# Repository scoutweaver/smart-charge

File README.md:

# smart-charge
This is the MCU coding which interacts with Raspberry pi sensors and a PostgreSQL database.
This system wil optimize the life of lithium ion batteries by enhancing the charging system.

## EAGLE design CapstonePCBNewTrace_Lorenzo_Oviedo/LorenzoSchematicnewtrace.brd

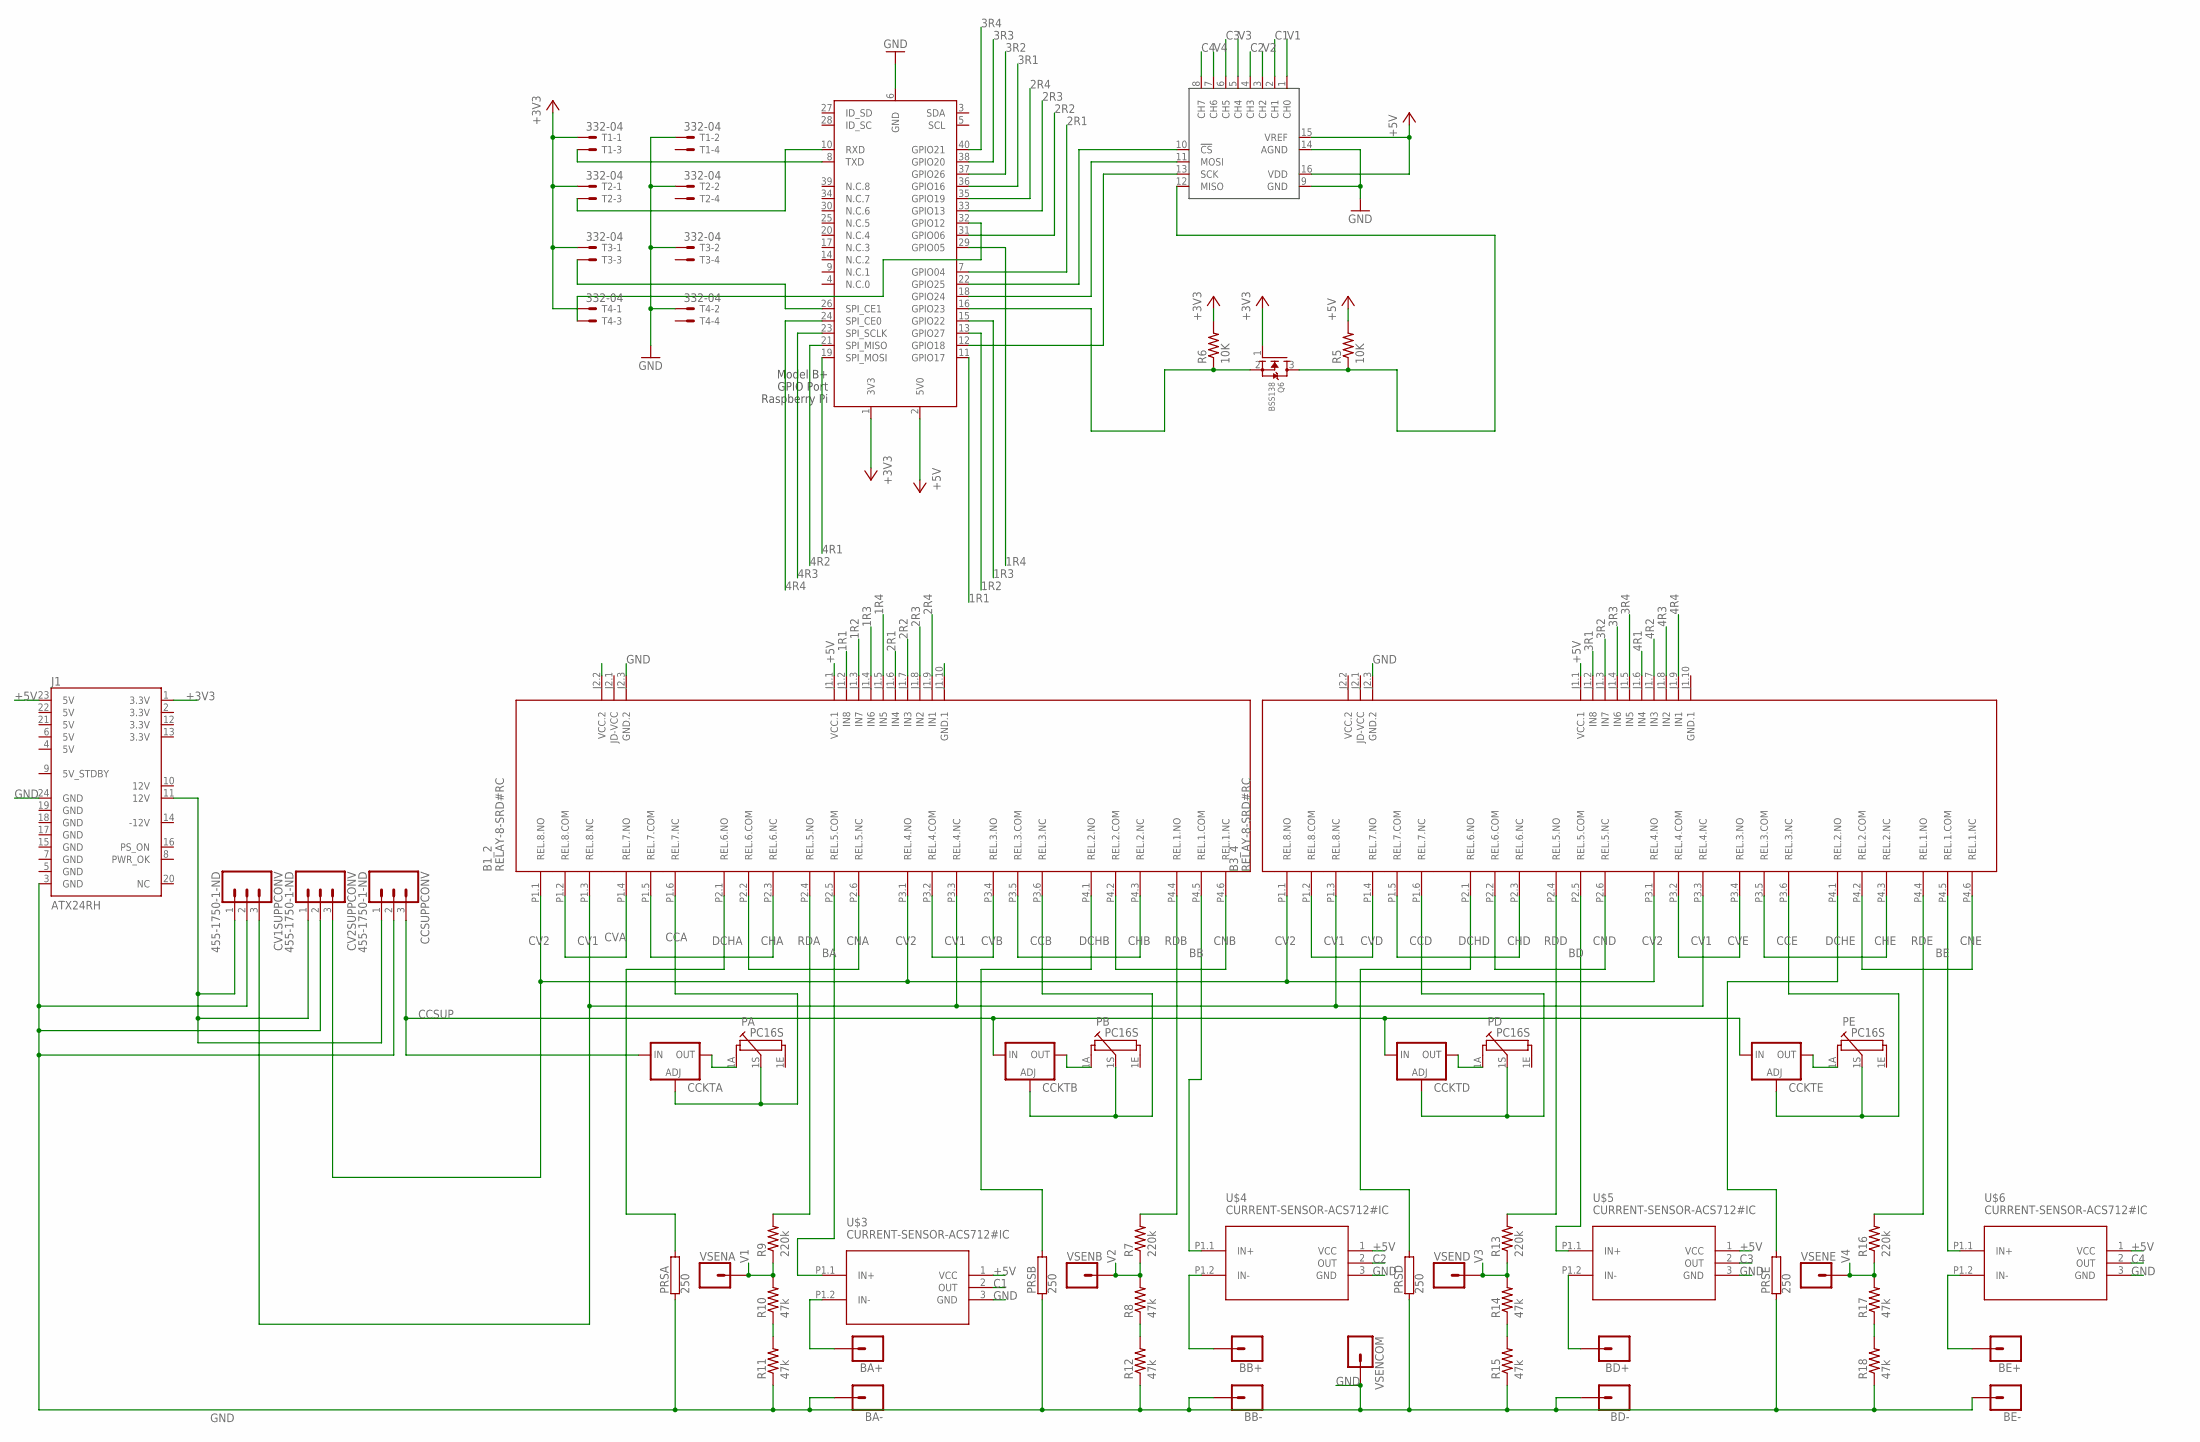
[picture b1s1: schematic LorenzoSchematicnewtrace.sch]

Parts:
ADC: MCP3008P; DIL16
B1_2, B3_4: RELAY-8-SRD#RC
BA+: CONN_01; 1X01
BA-: CONN_01; 1X01
BB+: CONN_01; 1X01
BB-: CONN_01; 1X01
BD+: CONN_01; 1X01
BD-: CONN_01; 1X01
BE+: CONN_01; 1X01
BE-: CONN_01; 1X01
CCKTA: LM317TL; 317TL
CCKTB: LM317TL; 317TL
CCKTD: LM317TL; 317TL
CCKTE: LM317TL; 317TL
CCSUPPCONV: 455-1750-1-ND; 1X03
CV1SUPPCONV, CV2SUPPCONV: 455-1750-1-ND; 1X03
J1: ATX24RH; ATX24_RIGHT_ANGLE
PA: PC16S
PB: PC16S
PD: PC16S
PE: PC16S
PRSA: 250; KH208-8
PRSB: 250; KH208-8
PRSD: 250; KH208-8
PRSE: 250; KH208-8
Q6: BSS138; SOT23
R5, R6: 10K; R0805
R7, R9, R13, R16: 220k; 0207/12
R8, R10, R11, R12, R14, R15, R17, R18: 47k; 0207/12
T1, T2, T3, T4: 332-04
U$3, U$4, U$5, U$6: CURRENT-SENSOR-ACS712#IC
VSENA: CONN_01; 1X01
VSENB: CONN_01; 1X01
VSENCOM: CONN_01; 1X01
VSEND: CONN_01; 1X01
VSENE: CONN_01; 1X01
X2: RASPI_BOARD_B+_E4; RASPI_BOARD_B+_EDGES_4DRILL

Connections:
1R1: B1_2.J1.2 (IN8), X2.11 (GPIO17)
1R2: B1_2.J1.3 (IN7), X2.13 (GPIO27)
1R3: B1_2.J1.4 (IN6), X2.15 (GPIO22)
1R4: B1_2.J1.5 (IN5), X2.29 (GPIO05)
2R1: B1_2.J1.6 (IN4), X2.7 (GPIO04)
2R2: B1_2.J1.7 (IN3), X2.31 (GPIO06)
2R3: B1_2.J1.8 (IN2), X2.33 (GPIO13)
2R4: B1_2.J1.9 (IN1), X2.35 (GPIO19)
3R1: B3_4.J1.2 (IN8), X2.36 (GPIO16)
3R2: B3_4.J1.3 (IN7), X2.37 (GPIO26)
3R3: B3_4.J1.4 (IN6), X2.38 (GPIO20)
3R4: B3_4.J1.5 (IN5), X2.40 (GPIO21)
4R1: B3_4.J1.6 (IN4), X2.19 (SPI_MOSI)
4R2: B3_4.J1.7 (IN3), X2.21 (SPI_MISO)
4R3: B3_4.J1.8 (IN2), X2.23 (SPI_SCLK)
4R4: B3_4.J1.9 (IN1), X2.24 (SPI_CE0)
12V: CCSUPPCONV.1, CV1SUPPCONV.1, CV2SUPPCONV.1, J1.11 (12V)
+3V3: J1.1 (3.3V), Q6.1 (G), R6.2, T1.1, T2.1, T3.1, T4.1, X2.1 (3V3)
+5V: ADC.15 (VREF), ADC.16 (VDD), B1_2.J1.1 (VCC.1), B3_4.J1.1 (VCC.1), J1.23 (5V), R5.2, U$3.1 (VCC), U$4.1 (VCC), U$5.1 (VCC), U$6.1 (VCC), X2.2 (5V0)
BA: B1_2.P2.5 (REL.5.COM), U$3.P1.1 (IN+)
BB: B1_2.P4.5 (REL.1.COM), U$4.P1.1 (IN+)
BD: B3_4.P2.5 (REL.5.COM), U$5.P1.1 (IN+)
BE: B3_4.P4.5 (REL.1.COM), U$6.P1.1 (IN+)
C1: ADC.2 (CH1), U$3.2 (OUT)
C2: ADC.4 (CH3), U$4.2 (OUT)
C3: ADC.6 (CH5), U$5.2 (OUT)
C4: ADC.8 (CH7), U$6.2 (OUT)
CCA: B1_2.P1.6 (REL.7.NC), CCKTA.1 (ADJ), PA.1S
CCB: B1_2.P3.6 (REL.3.NC), CCKTB.1 (ADJ), PB.1S
CCD: B3_4.P1.6 (REL.7.NC), CCKTD.1 (ADJ), PD.1S
CCE: B3_4.P3.6 (REL.3.NC), CCKTE.1 (ADJ), PE.1S
CCSUP: CCKTA.3 (IN), CCKTB.3 (IN), CCKTD.3 (IN), CCKTE.3 (IN), CCSUPPCONV.3
CHA: B1_2.P1.5 (REL.7.COM), B1_2.P2.3 (REL.6.NC)
CHB: B1_2.P3.5 (REL.3.COM), B1_2.P4.3 (REL.2.NC)
CHD: B3_4.P1.5 (REL.7.COM), B3_4.P2.3 (REL.6.NC)
CHE: B3_4.P3.5 (REL.3.COM), B3_4.P4.3 (REL.2.NC)
CNA: B1_2.P2.2 (REL.6.COM), B1_2.P2.6 (REL.5.NC)
CNB: B1_2.P4.2 (REL.2.COM), B1_2.P4.6 (REL.1.NC)
CND: B3_4.P2.2 (REL.6.COM), B3_4.P2.6 (REL.5.NC)
CNE: B3_4.P4.2 (REL.2.COM), B3_4.P4.6 (REL.1.NC)
CV1: B1_2.P1.3 (REL.8.NC), B1_2.P3.3 (REL.4.NC), B3_4.P1.3 (REL.8.NC), B3_4.P3.3 (REL.4.NC), CV1SUPPCONV.3
CV2: B1_2.P1.1 (REL.8.NO), B1_2.P3.1 (REL.4.NO), B3_4.P1.1 (REL.8.NO), B3_4.P3.1 (REL.4.NO), CV2SUPPCONV.3
CVA: B1_2.P1.2 (REL.8.COM), B1_2.P1.4 (REL.7.NO)
CVB: B1_2.P3.2 (REL.4.COM), B1_2.P3.4 (REL.3.NO)
CVD: B3_4.P1.2 (REL.8.COM), B3_4.P1.4 (REL.7.NO)
CVE: B3_4.P3.2 (REL.4.COM), B3_4.P3.4 (REL.3.NO)
DCHA: B1_2.P2.1 (REL.6.NO), PRSA.2
DCHB: B1_2.P4.1 (REL.2.NO), PRSB.2
DCHD: B3_4.P2.1 (REL.6.NO), PRSD.2
DCHE: B3_4.P4.1 (REL.2.NO), PRSE.2
GND: ADC.9 (GND), ADC.14 (AGND), B1_2.J2.3 (GND.2), B3_4.J2.3 (GND.2), BA-.1, BB-.1, BD-.1, BE-.1, CCSUPPCONV.2, CV1SUPPCONV.2, CV2SUPPCONV.2, J1.3 (GND), J1.24 (GND), PRSA.1, PRSB.1, PRSD.1, PRSE.1, R11.1, R12.1, R15.1, R18.1, T1.2, T2.2, T3.2, T4.2, U$3.3 (GND), U$4.3 (GND), U$5.3 (GND), U$6.3 (GND), VSENCOM.1, X2.6 (GND)
GND.1: B3_4.J1.10 (GND.1)
unnamed: CCKTA.2 (OUT), PA.1A
unnamed: CCKTB.2 (OUT), PB.1A
unnamed: Q6.2 (S), R6.1, X2.16 (GPIO23)
unnamed: R10.1, R11.2
unnamed: R8.1, R12.2
unnamed: CCKTD.2 (OUT), PD.1A
unnamed: R14.1, R15.2
unnamed: CCKTE.2 (OUT), PE.1A
unnamed: R17.1, R18.2
unnamed: ADC.12 (MISO), Q6.3 (D), R5.1
unnamed: T1.3, X2.8 (TXD)
unnamed: ADC.13 (SCK), X2.12 (GPIO18)
unnamed: ADC.11 (MOSI), X2.18 (GPIO24)
unnamed: ADC.10 (!CS), X2.22 (GPIO25)
unnamed: T2.3, X2.10 (RXD)
unnamed: T3.3, X2.26 (SPI_CE1)
unnamed: T4.3, X2.32 (GPIO12)
unnamed: BB+.1, U$4.P1.2 (IN-)
unnamed: BA+.1, U$3.P1.2 (IN-)
unnamed: BD+.1, U$5.P1.2 (IN-)
unnamed: BE+.1, U$6.P1.2 (IN-)
RDA: B1_2.P2.4 (REL.5.NO), R9.2
RDB: B1_2.P4.4 (REL.1.NO), R7.2
RDD: B3_4.P2.4 (REL.5.NO), R13.2
RDE: B3_4.P4.4 (REL.1.NO), R16.2
V1: ADC.1 (CH0), R9.1, R10.2, VSENA.1
V2: ADC.3 (CH2), R7.1, R8.2, VSENB.1
V3: ADC.5 (CH4), R13.1, R14.2, VSEND.1
V4: ADC.7 (CH6), R16.1, R17.2, VSENE.1
VCC.2: B3_4.J2.2 (VCC.2)

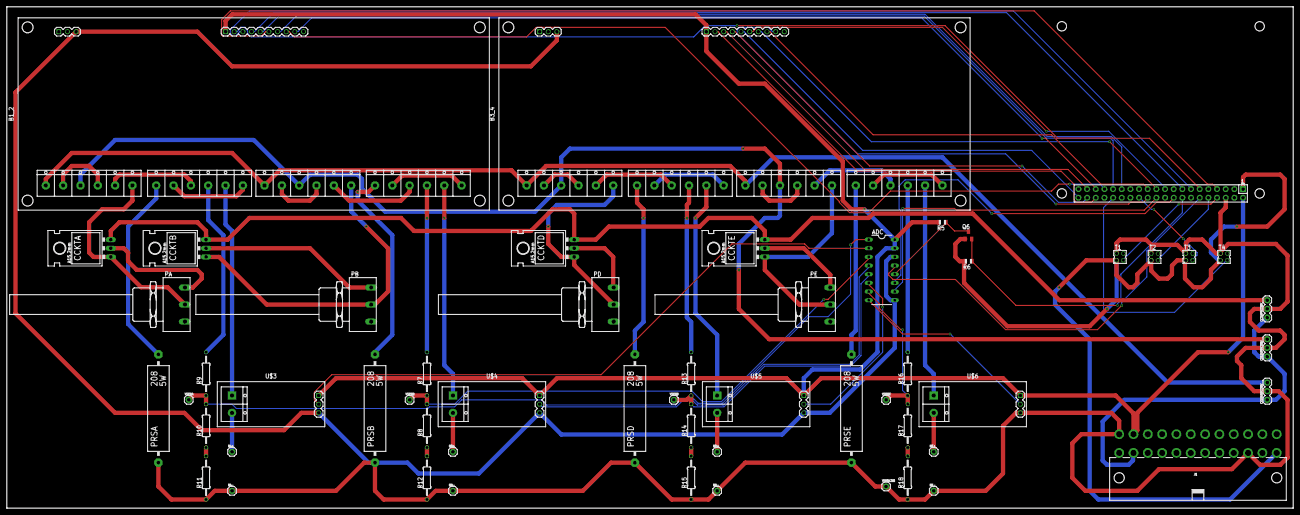
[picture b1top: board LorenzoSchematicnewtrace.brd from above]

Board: 2 copper layers, 377.2 x 147.0 mm, 56 parts (0 on the bottom side), 80 nets.

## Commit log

2017-11-07 Test for github
    I simply added a comment in order to test the operation of git-cola
2017-11-07 Fix topoff exit
    fixed a bug where after top off would nnot exxit
2018-05-01 testcommit
    testing how commits work
2018-05-01 final adjustments
2018-05-01 final commit, hopfully
2018-05-01 Other useful files
    Battery CAD holdaer for cells. Also PCB designs.

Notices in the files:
parts and their libraries:
SparkFun-Connectors: Licensing: Creative Commons ShareAlike 4.0 International - https://creativecommons.org/licenses/by-sa/4.0
diy-modules: Released under the Creative Commons Attribution 4.0 International License: http://creativecommons.org/licenses/by/4.0
